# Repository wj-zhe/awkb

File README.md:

# AWKB - A Weird Keyboard

Nothing fancy, just another Seeed Studio Xiao RP2040 based 36key split keyboard with features like
Japanese Matrix, trackball (pmw3360 based sensor), rotary encoder, and etc.

hardware: https://github.com/wj-zhe/awkb/tree/main/hardware/rev2  
firmware: https://github.com/wj-zhe/awkb/tree/main/firmware/rev2

optical sensor: https://github.com/wj-zhe/optical-sensor

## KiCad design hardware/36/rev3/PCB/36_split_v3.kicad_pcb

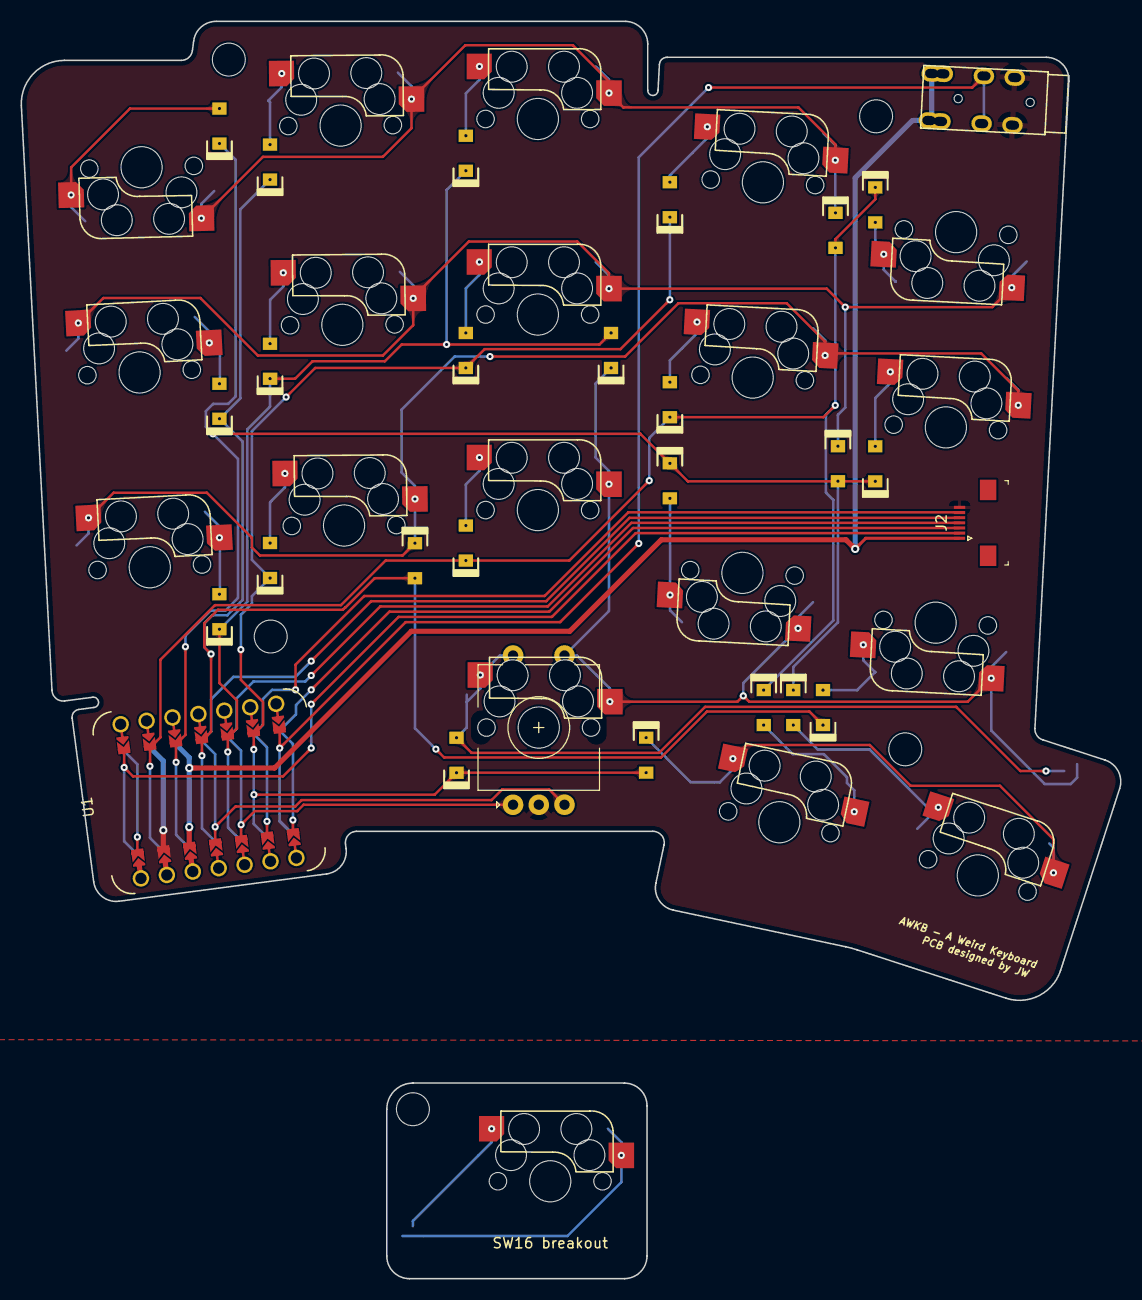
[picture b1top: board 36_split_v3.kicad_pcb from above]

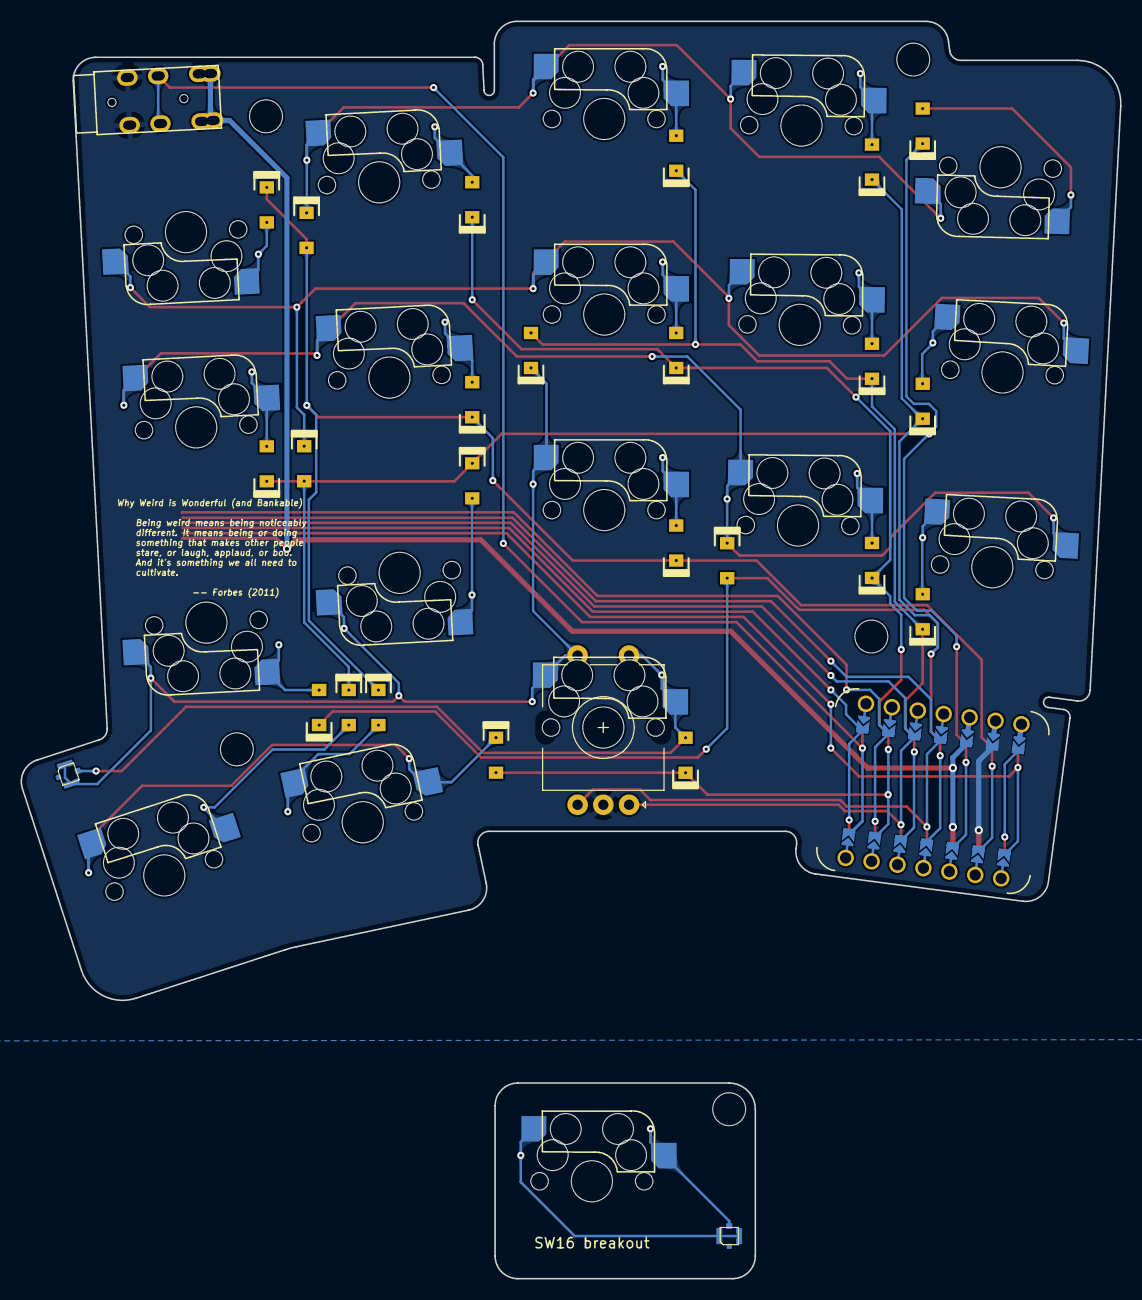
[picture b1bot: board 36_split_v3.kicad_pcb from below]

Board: 2 copper layers, 106.8 x 95.1 mm, 53 parts (3 on the bottom side), 38 nets.

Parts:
D1, D2, D3, D4, D5, D6, D7, D8, D9, D10, D11, D12, D13, D14, D15, D16, D17, D18: Diode; Diode_SOD123_THT_v3
D-1, D-2, D-3, D-4, D-5: Diode; Diode_SOD123_THT_v3
EC1: Rotary_Encoder_Switch; RotaryEncoder_Alps_EC11E-Switch_Vertical_H20mm_no_copper_MP
J1: 4PIN; TRRS-PJ-DPB2_mod
J2: Conn_01x07_Female; Conn_1x07-1MP_P0.5mm_Horizontal_Flip
J3, J4: Conn_Coaxial; Coaxial_MHF_2D_MHF_4_RECEPTACLE_20449_1C22_IPEX_4
SW1: SW1; CherryMX_Hotswap
SW2: SW2; CherryMX_Hotswap
SW3: SW3; CherryMX_Hotswap
SW4: SW4; CherryMX_Hotswap
SW5: SW5; CherryMX_Hotswap
SW6: SW6; CherryMX_Hotswap
SW7: SW7; CherryMX_Hotswap
SW8: SW8; CherryMX_Hotswap
SW9: SW9; CherryMX_Hotswap
SW10: SW10; CherryMX_Hotswap
SW11: SW11; CherryMX_Hotswap
SW12: SW12; CherryMX_Hotswap
SW13: SW13; CherryMX_Hotswap
SW14: SW14; CherryMX_Hotswap
SW15: SW15; CherryMX_Hotswap
SW16: SW16; CherryMX_Hotswap
SW16-1: SW16-1; CherryMX_Hotswap
SW17: SW17; CherryMX_Hotswap
SW18: SW18; CherryMX_Hotswap
TH1, TH2, TH3, TH4: MountingHole_Pad; MountingHole_3.2mm_M3_ISO14580
THS_1: MountingHole_Pad; MountingHole_3.2mm_M3_ISO14580
U1: SeeeduinoXIAO; Xiao THT jumper pad_flipped

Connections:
3V3: J1.1, J1.4, J2.1, U1.12 (3V3)
DATA: J1.2, U1.7 (PB08_A6_D6_TX)
ES_In: D-4.1 (K), EC1.S1, J3.2 (Ext), SW13.2, SW14.1, SW15.1, SW16.2
ES_Out: D16.2 (A), EC1.S2, J3.1 (In), SW16.1
FSR: J2.2, U1.1 (PA02_A0_D0)
GND: EC1.C, J1.3, J2.7, U1.13 (GND)
MISO_ENCB: EC1.A, J2.4, U1.10 (PA5_A9_D9_MISO)
MOSI_ENCA: EC1.B, J2.5, U1.11 (PA6_A10_D10_MOSI)
NCS: J2.3, U1.8 (PB09_A7_D7_RX)
unnamed: D1.2 (A), SW1.2
unnamed: D2.2 (A), SW2.1
unnamed: D3.2 (A), SW3.1
unnamed: D4.2 (A), SW4.1
unnamed: D5.2 (A), SW5.2
unnamed: D6.2 (A), SW6.2
unnamed: D7.2 (A), SW7.1
unnamed: D8.2 (A), SW8.1
unnamed: D9.2 (A), SW9.1
unnamed: D10.2 (A), SW10.1
unnamed: D11.2 (A), SW11.2
unnamed: D12.2 (A), SW12.1
unnamed: D13.2 (A), SW13.1
unnamed: D14.2 (A), SW14.2
unnamed: D15.2 (A), SW15.2
unnamed: D17.2 (A), SW17.2
unnamed: D18.2 (A), SW18.1
unnamed: D-1.1 (K), SW1.1, SW2.2, SW3.2, SW4.2
unnamed: D-2.1 (K), SW5.1, SW6.1, SW7.2, SW8.2
unnamed: D-3.1 (K), SW9.2, SW10.2, SW11.1, SW12.2
unnamed: D-5.1 (K), SW17.1, SW18.2
unnamed: J4.2 (Ext), SW16-1.2
unnamed: J4.1 (In), SW16-1.1
SCLK: J2.6, U1.9 (PA7_A8_D8_SCK)
pin0: D5.1 (K), D9.1 (K), D13.1 (K), D17.1 (K), D-1.2 (A), U1.2 (PA4_A1_D1)
pin1: D1.1 (K), D10.1 (K), D14.1 (K), D18.1 (K), D-2.2 (A), U1.3 (PA10_A2_D2)
pin2: D2.1 (K), D6.1 (K), D15.1 (K), D-3.2 (A), U1.4 (PA11_A3_D3)
pin3: D3.1 (K), D7.1 (K), D11.1 (K), D-4.2 (A), U1.5 (PA8_A4_D4_SDA)
pin4: D4.1 (K), D8.1 (K), D12.1 (K), D16.1 (K), D-5.2 (A), U1.6 (PA9_A5_D5_SCL)

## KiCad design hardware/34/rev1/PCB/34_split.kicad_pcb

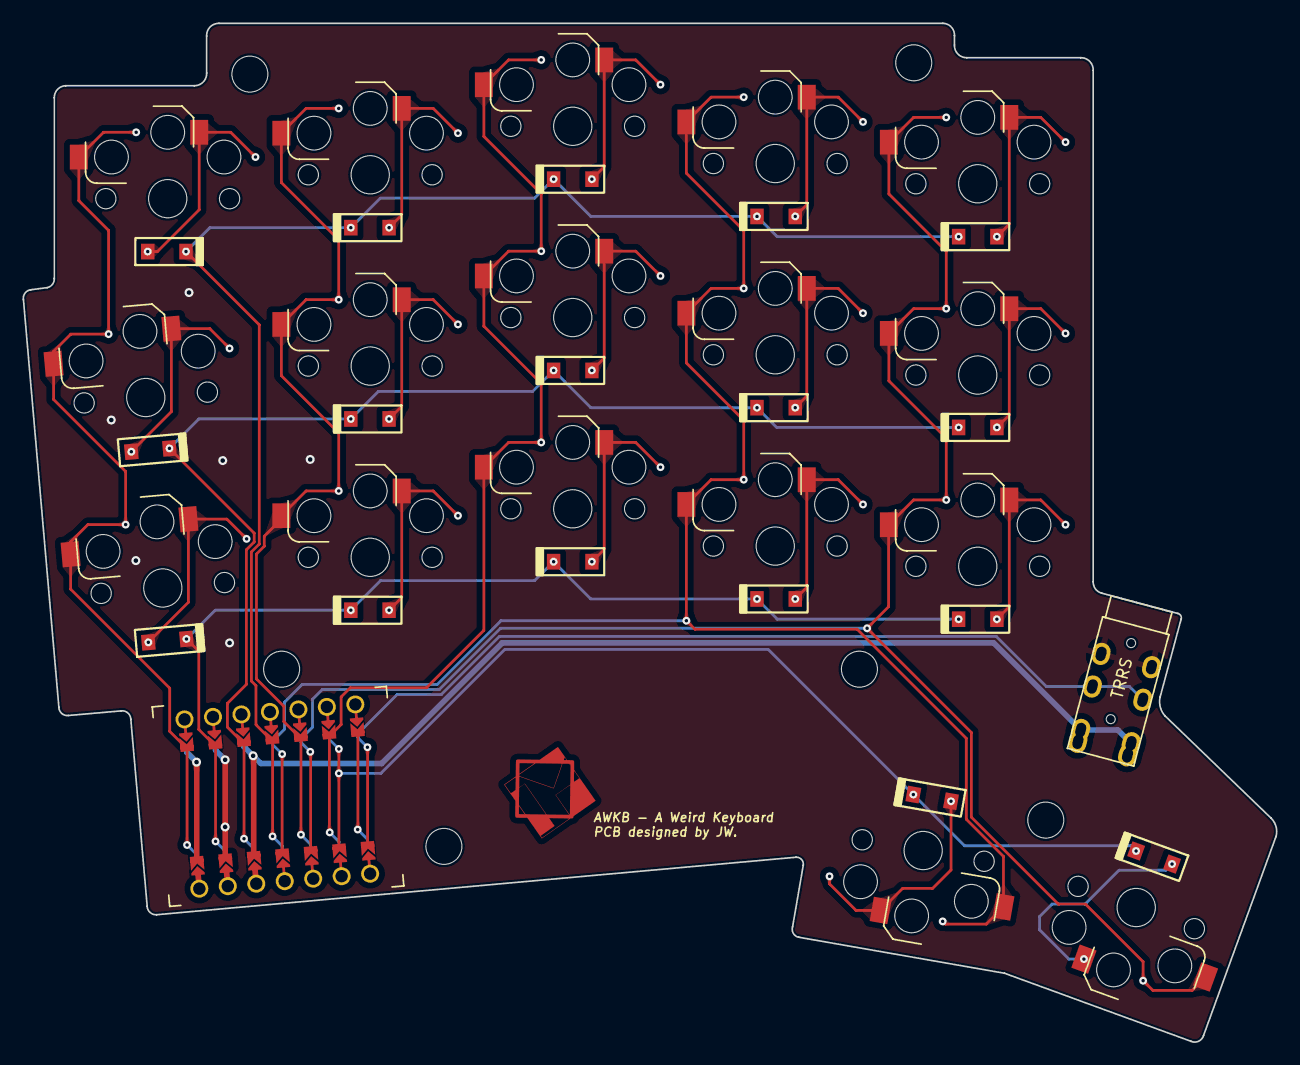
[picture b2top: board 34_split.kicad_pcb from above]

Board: 2 copper layers, 111.4 x 90.5 mm, 42 parts (0 on the bottom side), 29 nets.

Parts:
D1, D2, D3, D4, D5, D6, D7, D8, D9, D10, D11, D12, D13, D14, D15, D16, D17: D; Diode_SOD123_wo_THT
J1: 4PIN; TRRS-PJ-DPB2_mod
SW1: SW1; Kailh_Choc_PG1350_Hotswap_reversible
SW2: SW2; Kailh_Choc_PG1350_Hotswap_reversible
SW3: SW3; Kailh_Choc_PG1350_Hotswap_reversible
SW4: SW4; Kailh_Choc_PG1350_Hotswap_reversible
SW5: SW5; Kailh_Choc_PG1350_Hotswap_reversible
SW6: SW6; Kailh_Choc_PG1350_Hotswap_reversible
SW7: SW7; Kailh_Choc_PG1350_Hotswap_reversible
SW8: SW8; Kailh_Choc_PG1350_Hotswap_reversible
SW9: SW9; Kailh_Choc_PG1350_Hotswap_reversible
SW10: SW10; Kailh_Choc_PG1350_Hotswap_reversible
SW11: SW11; Kailh_Choc_PG1350_Hotswap_reversible
SW12: SW12; Kailh_Choc_PG1350_Hotswap_reversible
SW13: SW13; Kailh_Choc_PG1350_Hotswap_reversible
SW14: SW14; Kailh_Choc_PG1350_Hotswap_reversible
SW15: SW15; Kailh_Choc_PG1350_Hotswap_reversible
SW16: SW16; Kailh_Choc_PG1350_Hotswap_reversible
SW17: SW17; Kailh_Choc_PG1350_Hotswap_reversible
TH1, TH2, TH3, TH4, TH5, TH6: HOLE; MountingHole_3.2mm_M3
U1: SeeeduinoXIAO; Xiao THT jumper pad_flipped

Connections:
DATA: J1.2, U1.8 (PB09_A7_D7_RX)
GND: J1.3, U1.13 (GND)
unnamed: D1.2 (A), SW1.2
unnamed: D2.2 (A), SW2.2
unnamed: D3.2 (A), SW3.2
unnamed: D4.2 (A), SW4.2
unnamed: D5.2 (A), SW5.2
unnamed: D6.2 (A), SW6.2
unnamed: D7.2 (A), SW7.2
unnamed: D8.2 (A), SW8.2
unnamed: D9.2 (A), SW9.2
unnamed: D10.2 (A), SW10.2
unnamed: D11.2 (A), SW11.2
unnamed: D12.2 (A), SW12.2
unnamed: D13.2 (A), SW13.2
unnamed: D14.2 (A), SW14.2
unnamed: D15.2 (A), SW15.2
unnamed: D16.2 (A), SW16.2
unnamed: D17.2 (A), SW17.2
VCC: J1.1, J1.4, U1.12 (3V3)
col0: SW1.1, SW6.1, SW11.1, U1.1 (PA02_A0_D0)
col1: SW2.1, SW7.1, SW12.1, U1.5 (PA8_A4_D4_SDA)
col2: SW3.1, SW8.1, SW13.1, U1.6 (PA9_A5_D5_SCL)
col3: SW4.1, SW9.1, SW14.1, SW16.1, U1.11 (PA6_A10_D10_MOSI)
col4: SW5.1, SW10.1, SW15.1, SW17.1, U1.10 (PA5_A9_D9_MISO)
row0: D1.1 (K), D2.1 (K), D3.1 (K), D4.1 (K), D5.1 (K), U1.4 (PA11_A3_D3)
row1: D6.1 (K), D7.1 (K), D8.1 (K), D9.1 (K), D10.1 (K), U1.3 (PA10_A2_D2)
row2: D11.1 (K), D12.1 (K), D13.1 (K), D14.1 (K), D15.1 (K), U1.2 (PA4_A1_D1)
row3: D16.1 (K), D17.1 (K), U1.9 (PA7_A8_D8_SCK)

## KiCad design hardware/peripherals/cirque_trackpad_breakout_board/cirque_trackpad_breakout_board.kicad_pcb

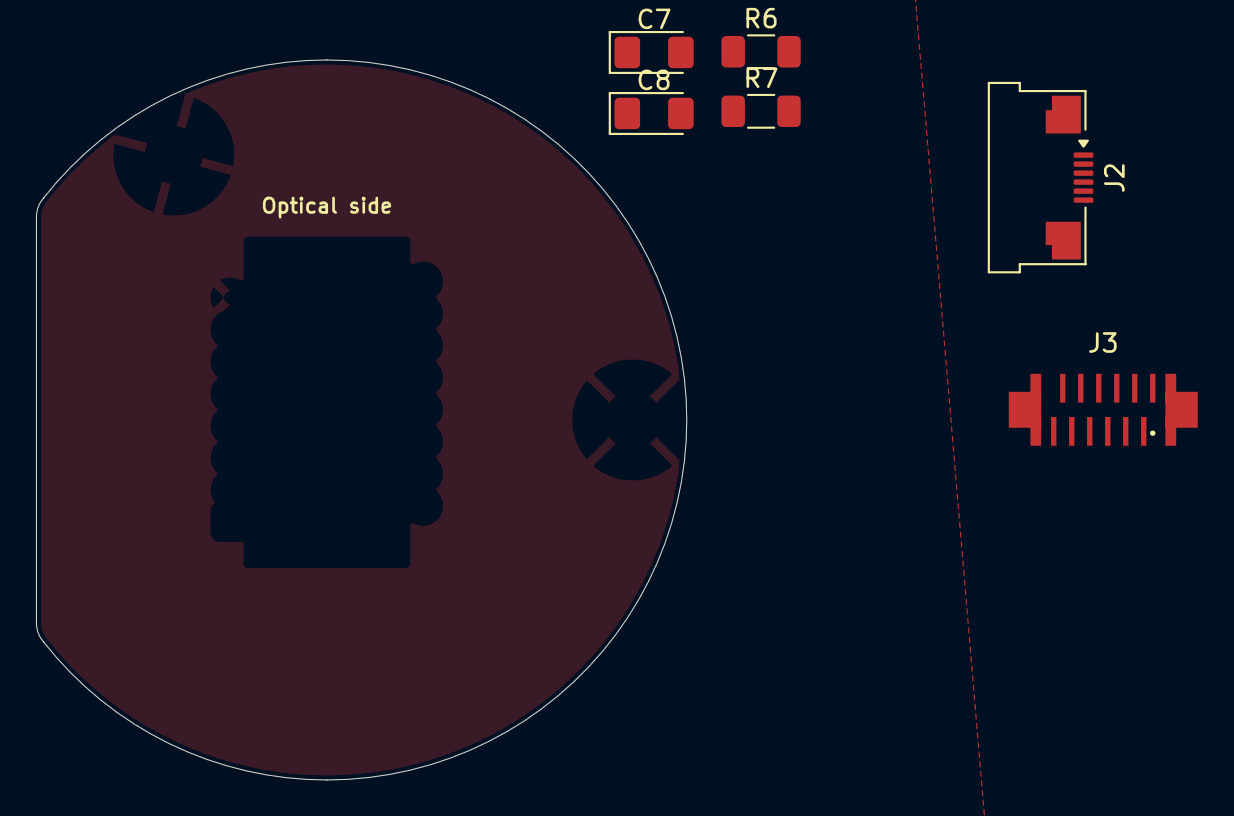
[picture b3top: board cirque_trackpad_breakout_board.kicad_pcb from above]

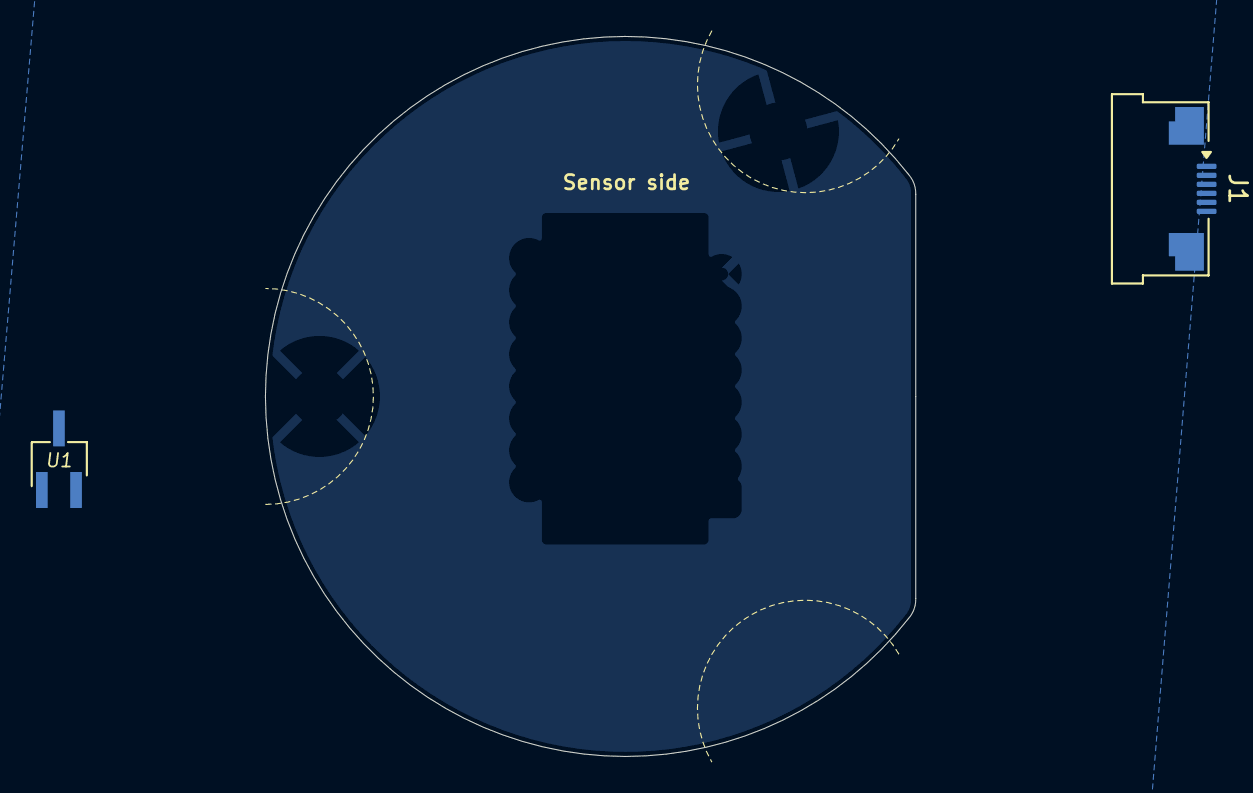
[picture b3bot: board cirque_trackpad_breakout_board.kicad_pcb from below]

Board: 2 copper layers, 36.1 x 40.0 mm, 8 parts (2 on the bottom side), 10 nets, no tracks yet.

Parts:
C7: 2.2uF; D_1206_3216Metric_Pad1.42x1.75mm_HandSolder
C8: 10uF; D_1206_3216Metric_Pad1.42x1.75mm_HandSolder
J1, J2: Conn_01x06; Amphenol_F32Q-1A7x1-11006_1x06-1MP_P0.5mm_Horizontal
J3: Conn_01x12; Hirose_FH12-12S-0.5SH_1x12-1MP_P0.50mm_Vertical_custom
R6, R7: 4.7k; R_1206_3216Metric_Pad1.30x1.75mm_HandSolder
U1: XC6206P332MR; TSOT-23_HandSoldering

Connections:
3V3: C7.1, J1.6, U1.3 (VI)
GND: J1.1, J2.4, J3.2
LDO_3v3: C8.1, J2.6, J3.1, R6.2, R7.2, U1.2 (VO)
MISO: J1.3, J3.11
MOSI: J1.2, J3.8
NCS: J1.5, J3.10
SCL: J2.3, J3.4, R6.1
SCLK: J1.4, J3.12
SDA: J2.5, J3.3, R7.1
_GND: C7.2, C8.2, U1.1 (GND)

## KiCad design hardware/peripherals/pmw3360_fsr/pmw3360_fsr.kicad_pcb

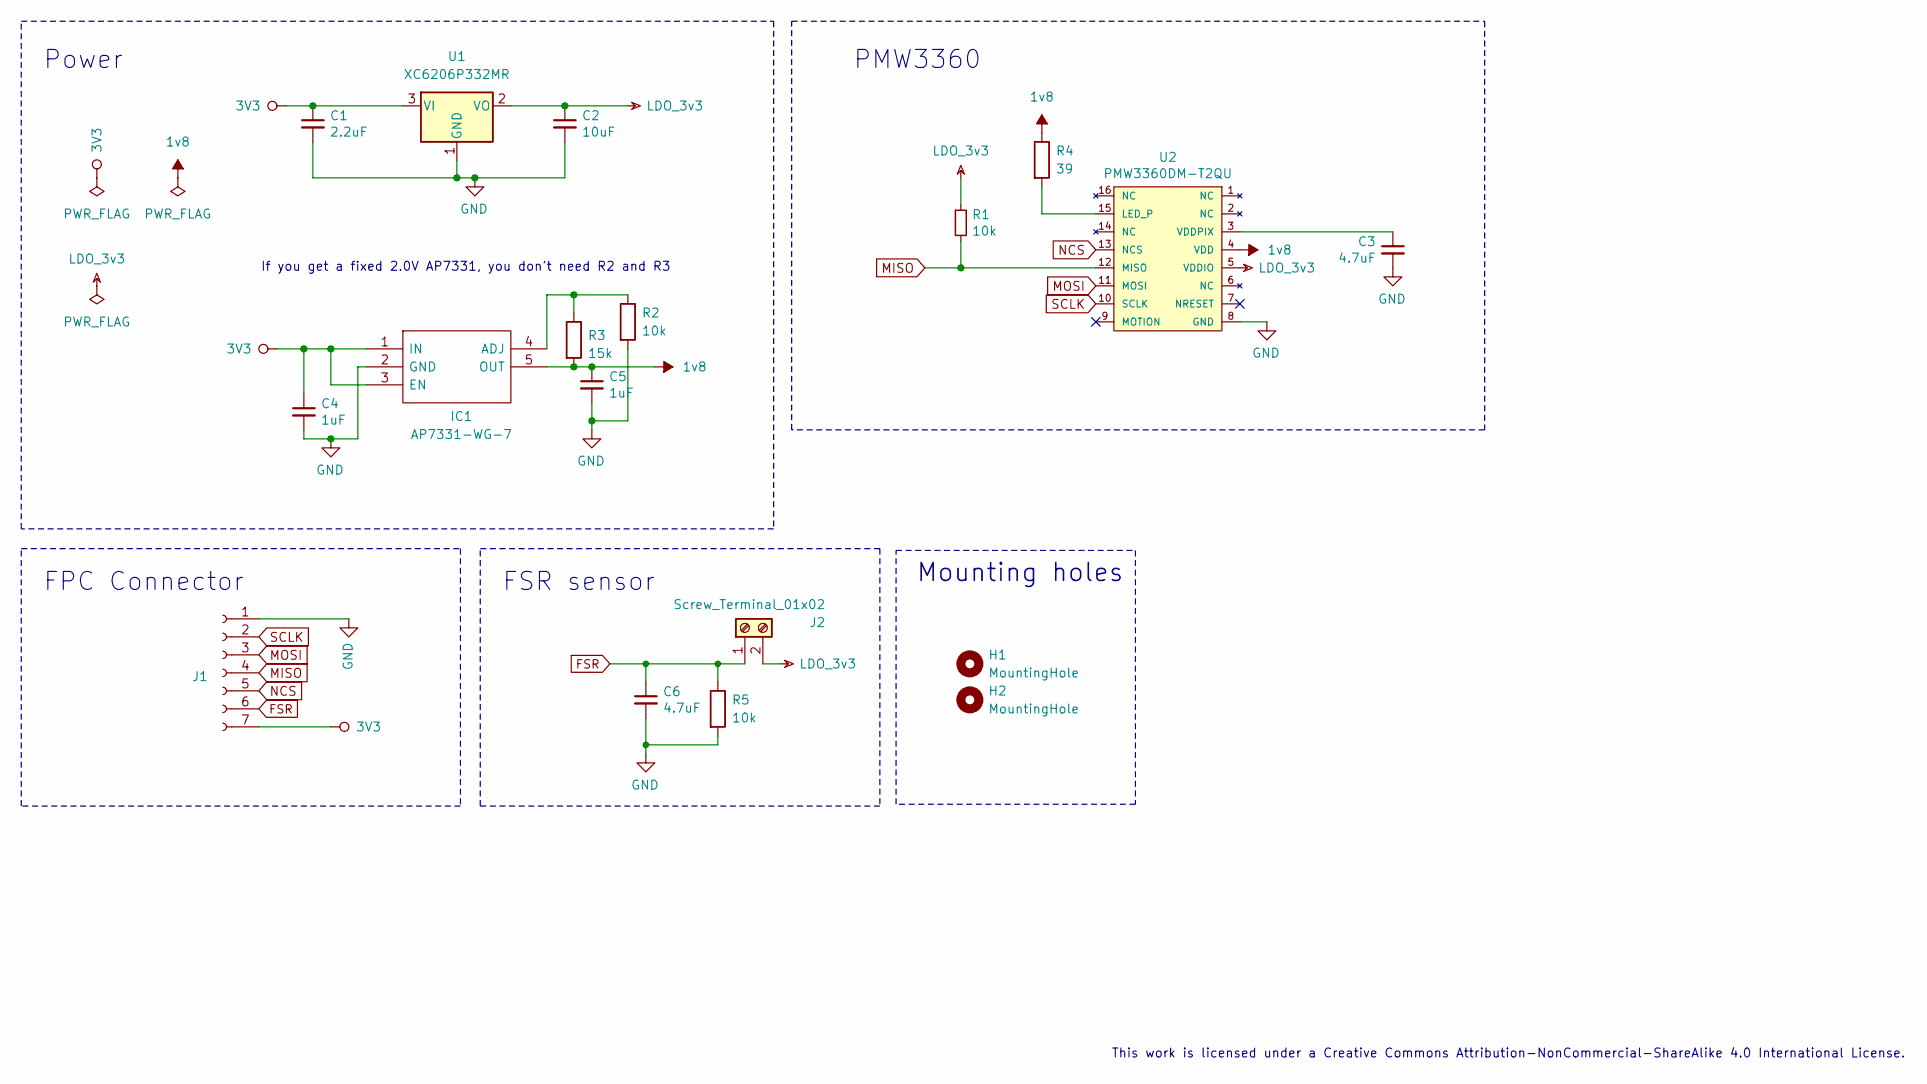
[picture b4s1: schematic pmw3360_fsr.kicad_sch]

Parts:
C1: 2.2uF; D_1206_3216Metric_Pad1.42x1.75mm_HandSolder; LCSC C1858
C2: 10uF; D_1206_3216Metric_Pad1.42x1.75mm_HandSolder; LCSC C152957
C3: 4.7uF; D_1206_3216Metric_Pad1.42x1.75mm_HandSolder; LCSC C29823
C4, C5: 1uF; D_1206_3216Metric_Pad1.42x1.75mm_HandSolder; LCSC C1926
C6: 4.7uF; D_1206_3216Metric_Pad1.42x1.75mm_HandSolder; LCSC C1858
H1, H2: MountingHole; MountingHole_3.2mm_M3
IC1: AP7331-WG-7; AP7331; Manufacturer_Part_Number AP7331-WG-7; Mouser Part Number 621-AP7331-WG-7
J1: Conn_01x07_Female; Conn_1x07-1MP_P0.5mm_Horizontal_Flip
J2: Screw_Terminal_01x02; TerminalBlock_Phoenix_MPT-0,5-2-2.54_1x02_P2.54mm_Horizontal
R1, R2, R5: 10k; D_1206_3216Metric_Pad1.42x1.75mm_HandSolder; LCSC C328409
R3: 15k; D_1206_3216Metric_Pad1.42x1.75mm_HandSolder; LCSC C351534
R4: 39; D_1206_3216Metric_Pad1.42x1.75mm_HandSolder; LCSC C153384
U1: XC6206P332MR; TSOT-23_HandSoldering; LCSC C347376
U2: PMW3360DM-T2QU; PMW3360DM_DIP-16_W10.16mm

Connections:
1v8: C5.1, IC1.5 (OUT), R3.2, R4.1, U2.4 (VDD)
3V3: C1.1, C4.1, IC1.1 (IN), IC1.3 (EN), J1.7, U1.3 (VI)
FSR: C6.1, J1.6, J2.1, R5.1
GND: C1.2, C2.2, C3.2, C4.2, C5.2, C6.2, IC1.2 (GND), J1.1, R2.2, R5.2, U1.1 (GND), U2.8 (GND)
LDO_3v3: C2.1, J2.2, R1.1, U1.2 (VO), U2.5 (VDDIO)
MISO: J1.4, R1.2, U2.12 (MISO)
MOSI: J1.3, U2.11 (MOSI)
NCS: J1.5, U2.13 (NCS)
unnamed: IC1.4 (ADJ), R2.1, R3.1
unnamed: R4.2, U2.15 (LED_P)
unnamed: C3.1, U2.3 (VDDPIX)
SCLK: J1.2, U2.10 (SCLK)

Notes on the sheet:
This work is licensed under a Creative Commons Attribution-NonCommercial-ShareAlike 4.0 International License.
Mounting holes
FSR sensor
If you get a fixed 2.0V AP7331, you don't need R2 and R3
Power
PMW3360
FPC Connector

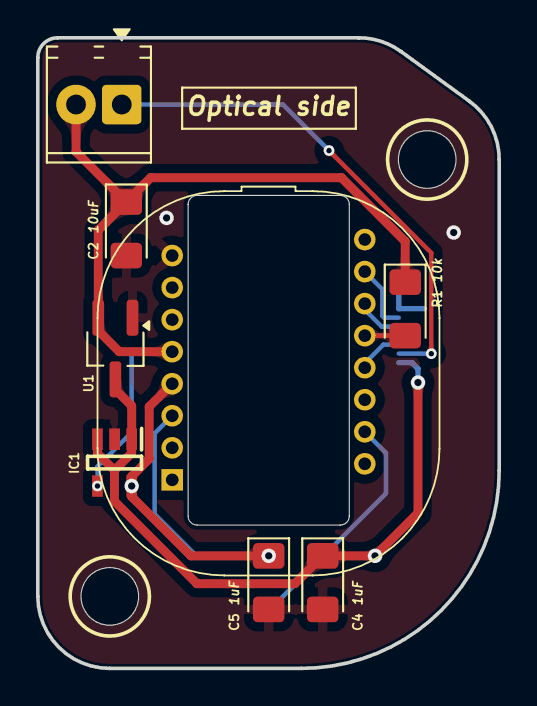
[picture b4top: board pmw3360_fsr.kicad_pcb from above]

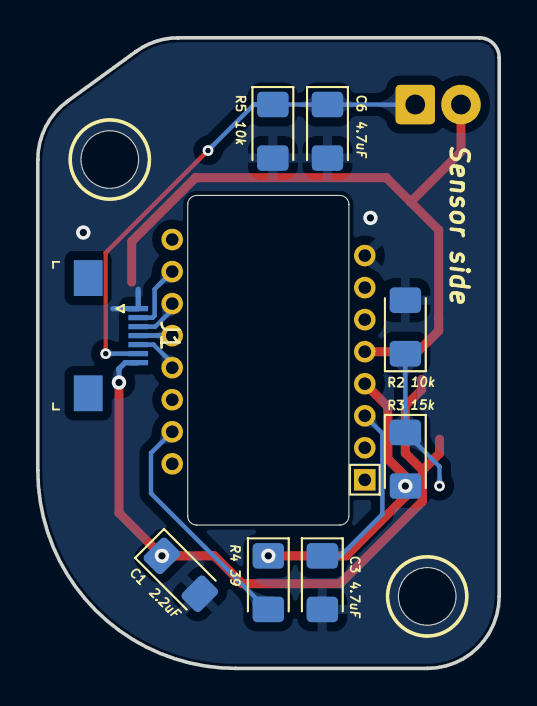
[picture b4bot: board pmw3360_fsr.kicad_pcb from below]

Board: 2 copper layers, 25.6 x 35.0 mm, 18 parts (9 on the bottom side), 12 nets.

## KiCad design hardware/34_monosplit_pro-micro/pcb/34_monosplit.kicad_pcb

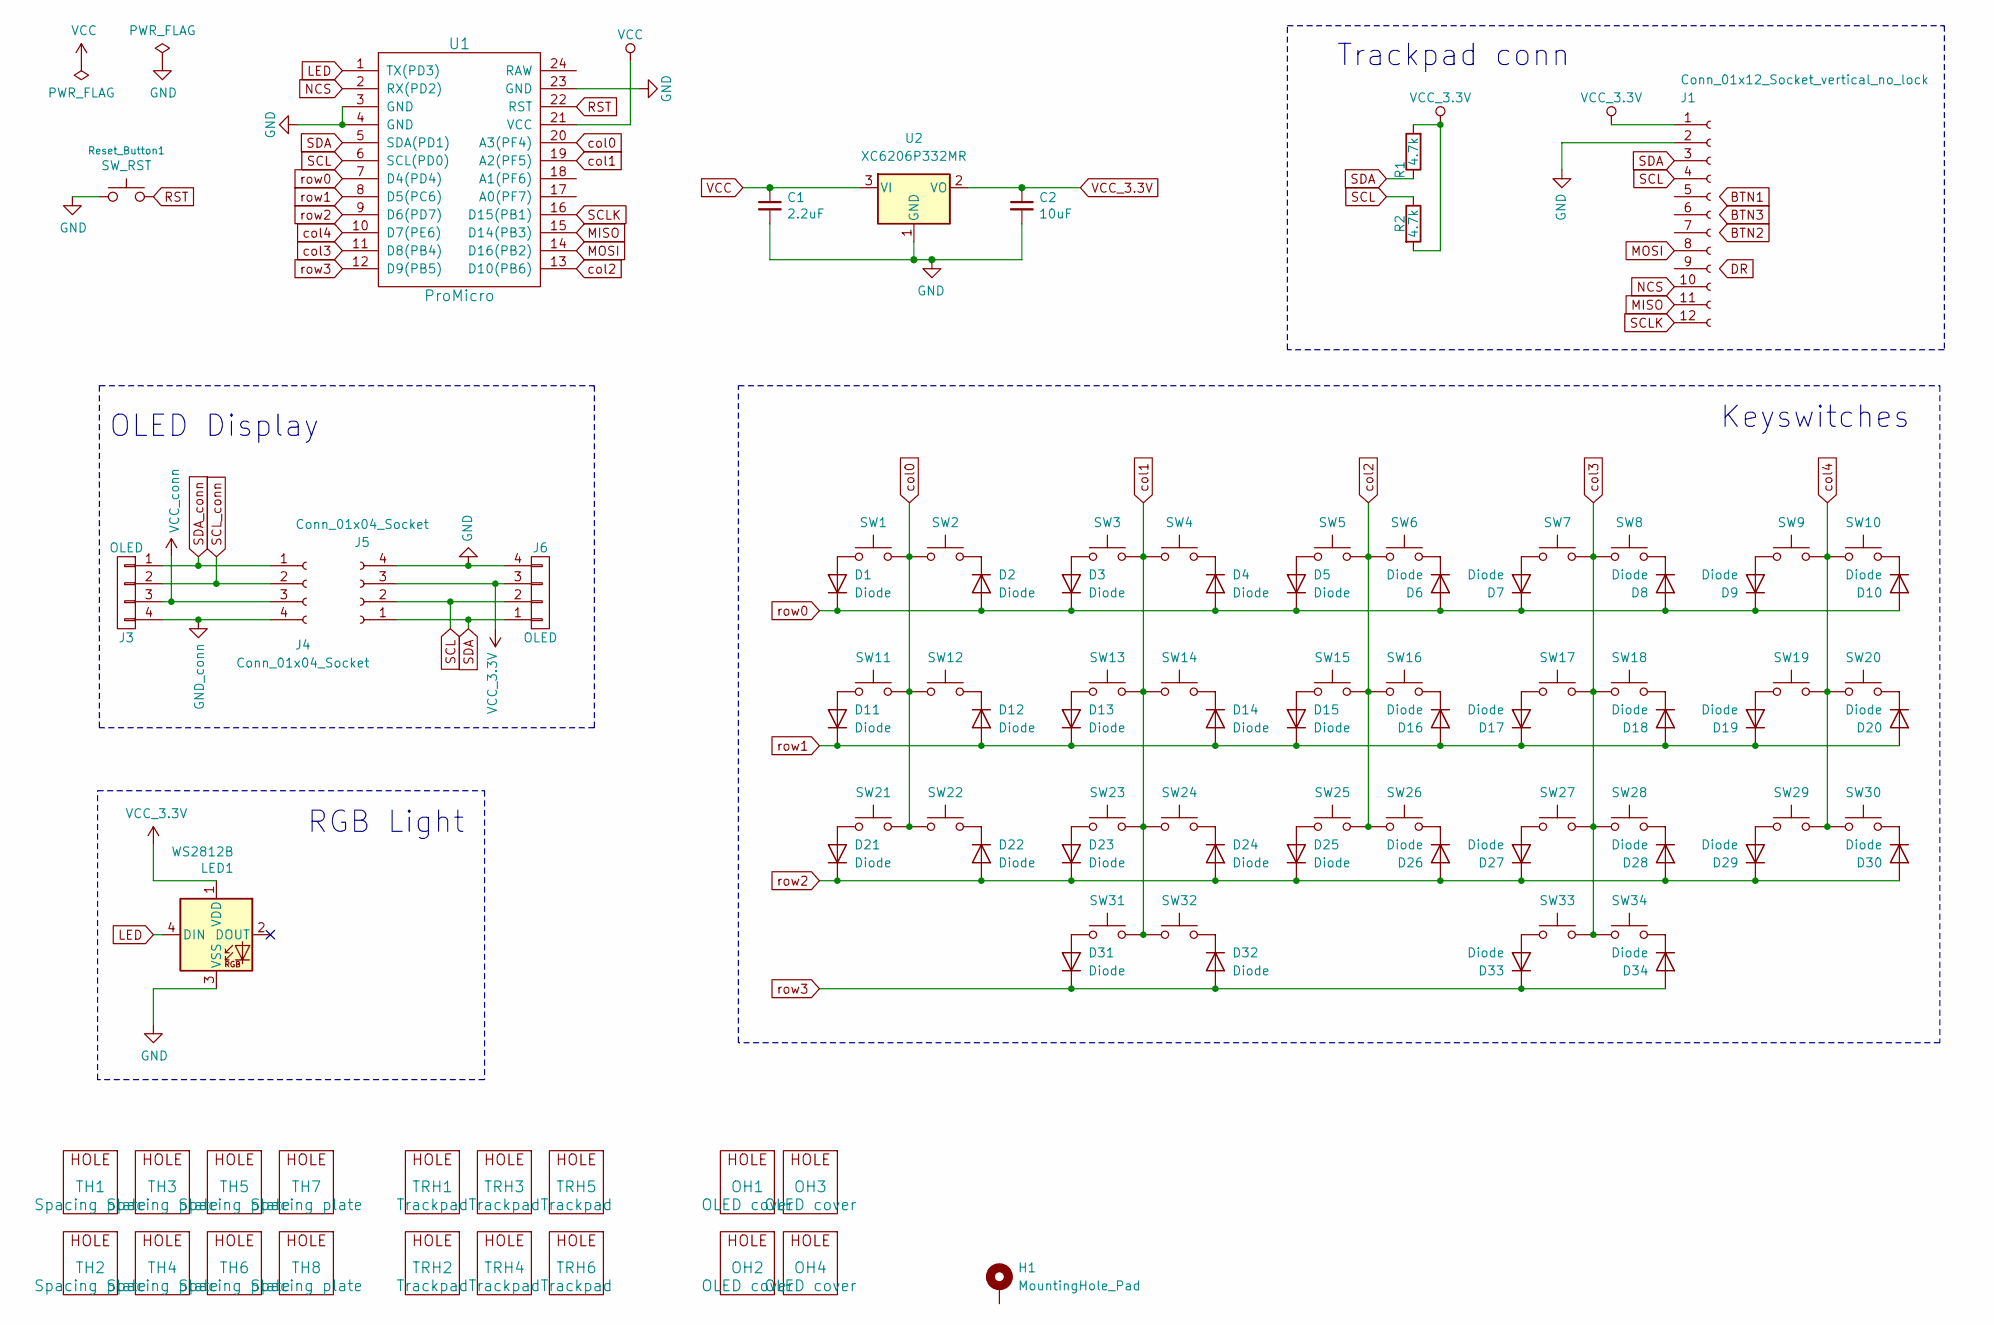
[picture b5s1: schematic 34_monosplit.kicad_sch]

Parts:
C1: 2.2uF; D_1206_3216Metric_Pad1.42x1.75mm_HandSolder; LCSC C1858
C2: 10uF; D_1206_3216Metric_Pad1.42x1.75mm_HandSolder; LCSC C152957
D1, D2, D3, D4, D5, D6, D7, D8, D9, D10, D11, D12, D13, D14, D15, D16, D17, D18, D19, D20, D21, D22, D23, D24, D25, D26, D27, D28, D29, D30, D31, D32, D33, D34: Diode; Diode_SOD123_SMD
H1: MountingHole_Pad; square_1
J1: Conn_01x12_Socket_vertical_no_lock; Hirose_FH12-12S-0.5SH_1x12-1MP_P0.50mm_Vertical_custom
J3, J6: OLED; PinSocket_1x04_P2.54mm_Vertical
J4, J5: Conn_01x04_Socket; Molex_200528-0040_1x04-1MP_P1.00mm_Horizontal
LED1: WS2812B; LED_WS2812B_PLCC4_5.0x5.0mm_P3.2mm
OH1, OH2, OH3, OH4: OLED cover; MountingHole_2.2mm_M2_ISO7380_Pad
R1, R2: 4.7k; R_1206_3216Metric_Pad1.30x1.75mm_HandSolder; LCSC C269746
Reset_Button1: SW_RST; SW_SPST_TL3342
SW1: SW1; CherryMX_Hotswap_single_side
SW2: SW2; CherryMX_Hotswap_single_side
SW3: SW3; CherryMX_Hotswap_single_side
SW4: SW4; CherryMX_Hotswap_single_side
SW5: SW5; CherryMX_Hotswap_single_side
SW6: SW6; CherryMX_Hotswap_single_side
SW7: SW7; CherryMX_Hotswap_single_side
SW8: SW8; CherryMX_Hotswap_single_side
SW9: SW9; CherryMX_Hotswap_single_side
SW10: SW10; CherryMX_Hotswap_single_side
SW11: SW11; CherryMX_Hotswap_single_side
SW12: SW12; CherryMX_Hotswap_single_side
SW13: SW13; CherryMX_Hotswap_single_side
SW14: SW14; CherryMX_Hotswap_single_side
SW15: SW15; CherryMX_Hotswap_single_side
SW16: SW16; CherryMX_Hotswap_single_side
SW17: SW17; CherryMX_Hotswap_single_side
SW18: SW18; CherryMX_Hotswap_single_side
SW19: SW19; CherryMX_Hotswap_single_side
SW20: SW20; CherryMX_Hotswap_single_side
SW21: SW21; CherryMX_Hotswap_single_side
SW22: SW22; CherryMX_Hotswap_single_side
SW23: SW23; CherryMX_Hotswap_single_side
SW24: SW24; CherryMX_Hotswap_single_side
SW25: SW25; CherryMX_Hotswap_single_side
SW26: SW26; CherryMX_Hotswap_single_side
SW27: SW27; CherryMX_Hotswap_single_side
SW28: SW28; CherryMX_Hotswap_single_side
SW29: SW29; CherryMX_Hotswap_single_side
SW30: SW30; CherryMX_Hotswap_single_side
SW31: SW31; CherryMX_Hotswap_single_side
SW32: SW32; CherryMX_Hotswap_single_side
SW33: SW33; CherryMX_Hotswap_single_side
SW34: SW34; CherryMX_Hotswap_single_side
TH1, TH2, TH3, TH4, TH5, TH6, TH7, TH8: Spacing plate; MountingHole_3.2mm_M3
TRH1, TRH2, TRH3, TRH4, TRH5, TRH6: Trackpad; MountingHole_3.2mm_M3
U1: ProMicro; ProMicro_1.1mm_hole_only
U2: XC6206P332MR; TSOT-23_HandSoldering; LCSC C347376

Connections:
GND: C1.2, C2.2, J1.2, J5.4, J6.4, LED1.3 (VSS), Reset_Button1.1, U1.3 (GND), U1.4 (GND), U1.23 (GND), U2.1 (GND)
GND_conn: J3.4, J4.4
LED: LED1.4 (DIN), U1.1 (TX(PD3))
MISO: J1.11, U1.15 (D14(PB3))
MOSI: J1.8, U1.14 (D16(PB2))
NCS: J1.10, U1.2 (RX(PD2))
unnamed: D1.2 (A), SW1.1
unnamed: D2.1 (K), SW2.2
unnamed: D3.2 (A), SW3.1
unnamed: D4.1 (K), SW4.2
unnamed: D5.2 (A), SW5.1
unnamed: D6.1 (K), SW6.2
unnamed: D7.2 (A), SW7.1
unnamed: D8.1 (K), SW8.2
unnamed: D9.2 (A), SW9.1
unnamed: D10.1 (K), SW10.2
unnamed: D11.2 (A), SW11.1
unnamed: D12.1 (K), SW12.2
unnamed: D13.2 (A), SW13.1
unnamed: D14.1 (K), SW14.2
unnamed: D15.2 (A), SW15.1
unnamed: D16.1 (K), SW16.2
unnamed: D17.2 (A), SW17.1
unnamed: D18.1 (K), SW18.2
unnamed: D19.2 (A), SW19.1
unnamed: D20.1 (K), SW20.2
unnamed: D21.2 (A), SW21.1
unnamed: D22.1 (K), SW22.2
unnamed: D23.2 (A), SW23.1
unnamed: D24.1 (K), SW24.2
unnamed: D25.2 (A), SW25.1
unnamed: D26.1 (K), SW26.2
unnamed: D27.2 (A), SW27.1
unnamed: D28.1 (K), SW28.2
unnamed: D29.2 (A), SW29.1
unnamed: D30.1 (K), SW30.2
unnamed: D31.2 (A), SW31.1
unnamed: D32.1 (K), SW32.2
unnamed: D33.2 (A), SW33.1
unnamed: D34.1 (K), SW34.2
RST: Reset_Button1.2, U1.22 (RST)
SCL: J1.4, J5.2, J6.2, R2.1, U1.6 (SCL(PD0))
SCLK: J1.12, U1.16 (D15(PB1))
SCL_conn: J3.2, J4.2
SDA: J1.3, J5.1, J6.1, R1.1, U1.5 (SDA(PD1))
SDA_conn: J3.1, J4.1
VCC: C1.1, U1.21 (VCC), U2.3 (VI)
VCC_3.3V: C2.1, J1.1, J5.3, J6.3, LED1.1 (VDD), R1.2, R2.2, U2.2 (VO)
VCC_conn: J3.3, J4.3
col0: SW1.2, SW2.1, SW11.2, SW12.1, SW21.2, SW22.1, U1.20 (A3(PF4))
col1: SW3.2, SW4.1, SW13.2, SW14.1, SW23.2, SW24.1, SW31.2, SW32.1, U1.19 (A2(PF5))
col2: SW5.2, SW6.1, SW15.2, SW16.1, SW25.2, SW26.1, U1.13 (D10(PB6))
col3: SW7.2, SW8.1, SW17.2, SW18.1, SW27.2, SW28.1, SW33.2, SW34.1, U1.11 (D8(PB4))
col4: SW9.2, SW10.1, SW19.2, SW20.1, SW29.2, SW30.1, U1.10 (D7(PE6))
row0: D1.1 (K), D2.2 (A), D3.1 (K), D4.2 (A), D5.1 (K), D6.2 (A), D7.1 (K), D8.2 (A), D9.1 (K), D10.2 (A), U1.7 (D4(PD4))
row1: D11.1 (K), D12.2 (A), D13.1 (K), D14.2 (A), D15.1 (K), D16.2 (A), D17.1 (K), D18.2 (A), D19.1 (K), D20.2 (A), U1.8 (D5(PC6))
row2: D21.1 (K), D22.2 (A), D23.1 (K), D24.2 (A), D25.1 (K), D26.2 (A), D27.1 (K), D28.2 (A), D29.1 (K), D30.2 (A), U1.9 (D6(PD7))
row3: D31.1 (K), D32.2 (A), D33.1 (K), D34.2 (A), U1.12 (D9(PB5))

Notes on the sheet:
RGB Light
Trackpad conn
OLED Display
Keyswitches

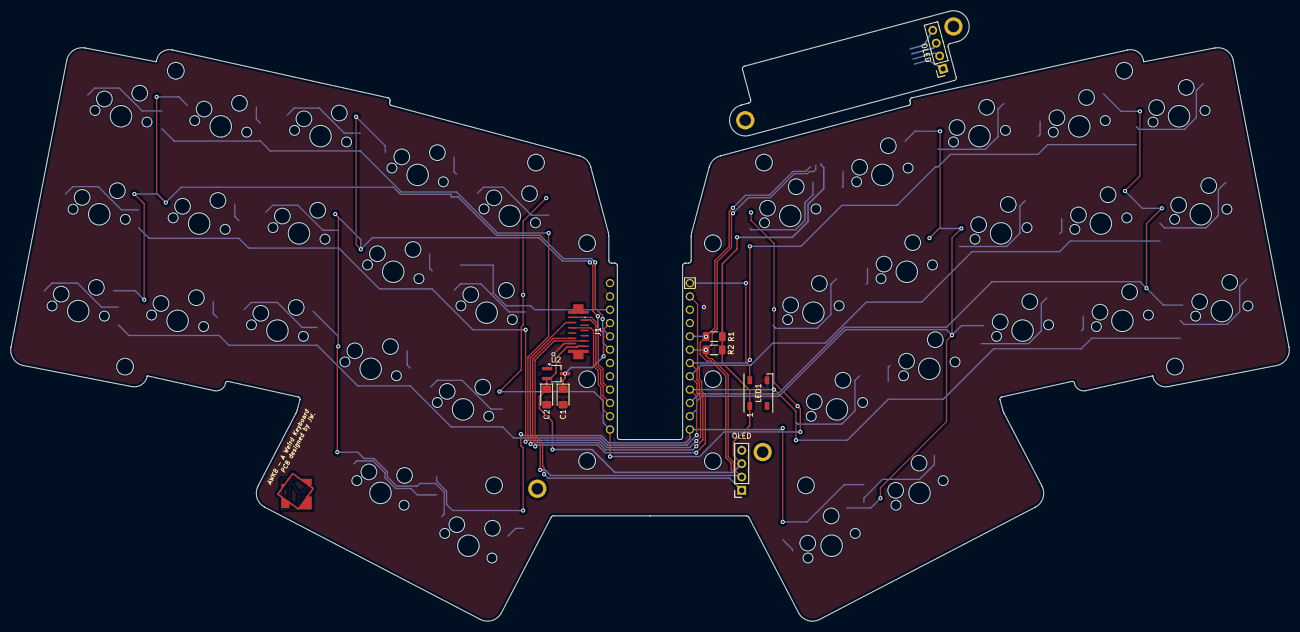
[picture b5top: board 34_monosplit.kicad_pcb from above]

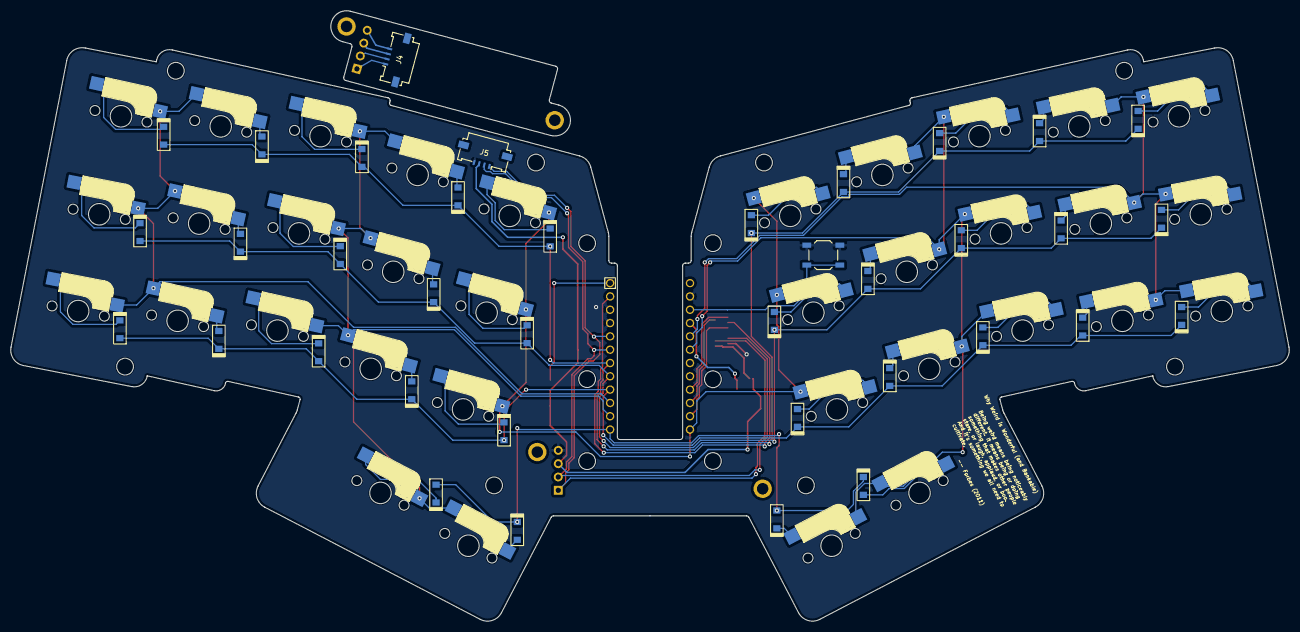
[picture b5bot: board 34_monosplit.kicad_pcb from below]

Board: 2 copper layers, 243.9 x 116.5 mm, 100 parts (38 on the bottom side), 58 nets.

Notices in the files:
hardware/peripherals/pmw3360_fsr/pmw3360_fsr.kicad_sch:
Copyright Quentin Lebastard
